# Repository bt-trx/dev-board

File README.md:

# bt-trx-dev-board

## BOM Generation

https://github.com/SchrodingersGat/KiBoM

### Installation

"Tools" -> "Generate Bill of Materials" -> New Plugin

### Benutzung

Eintragen der Bestellnummern ueber Properties des einzelnen Bauteils, oder gesammelt ueber "Tools"->"Edit Symbol Fields..."

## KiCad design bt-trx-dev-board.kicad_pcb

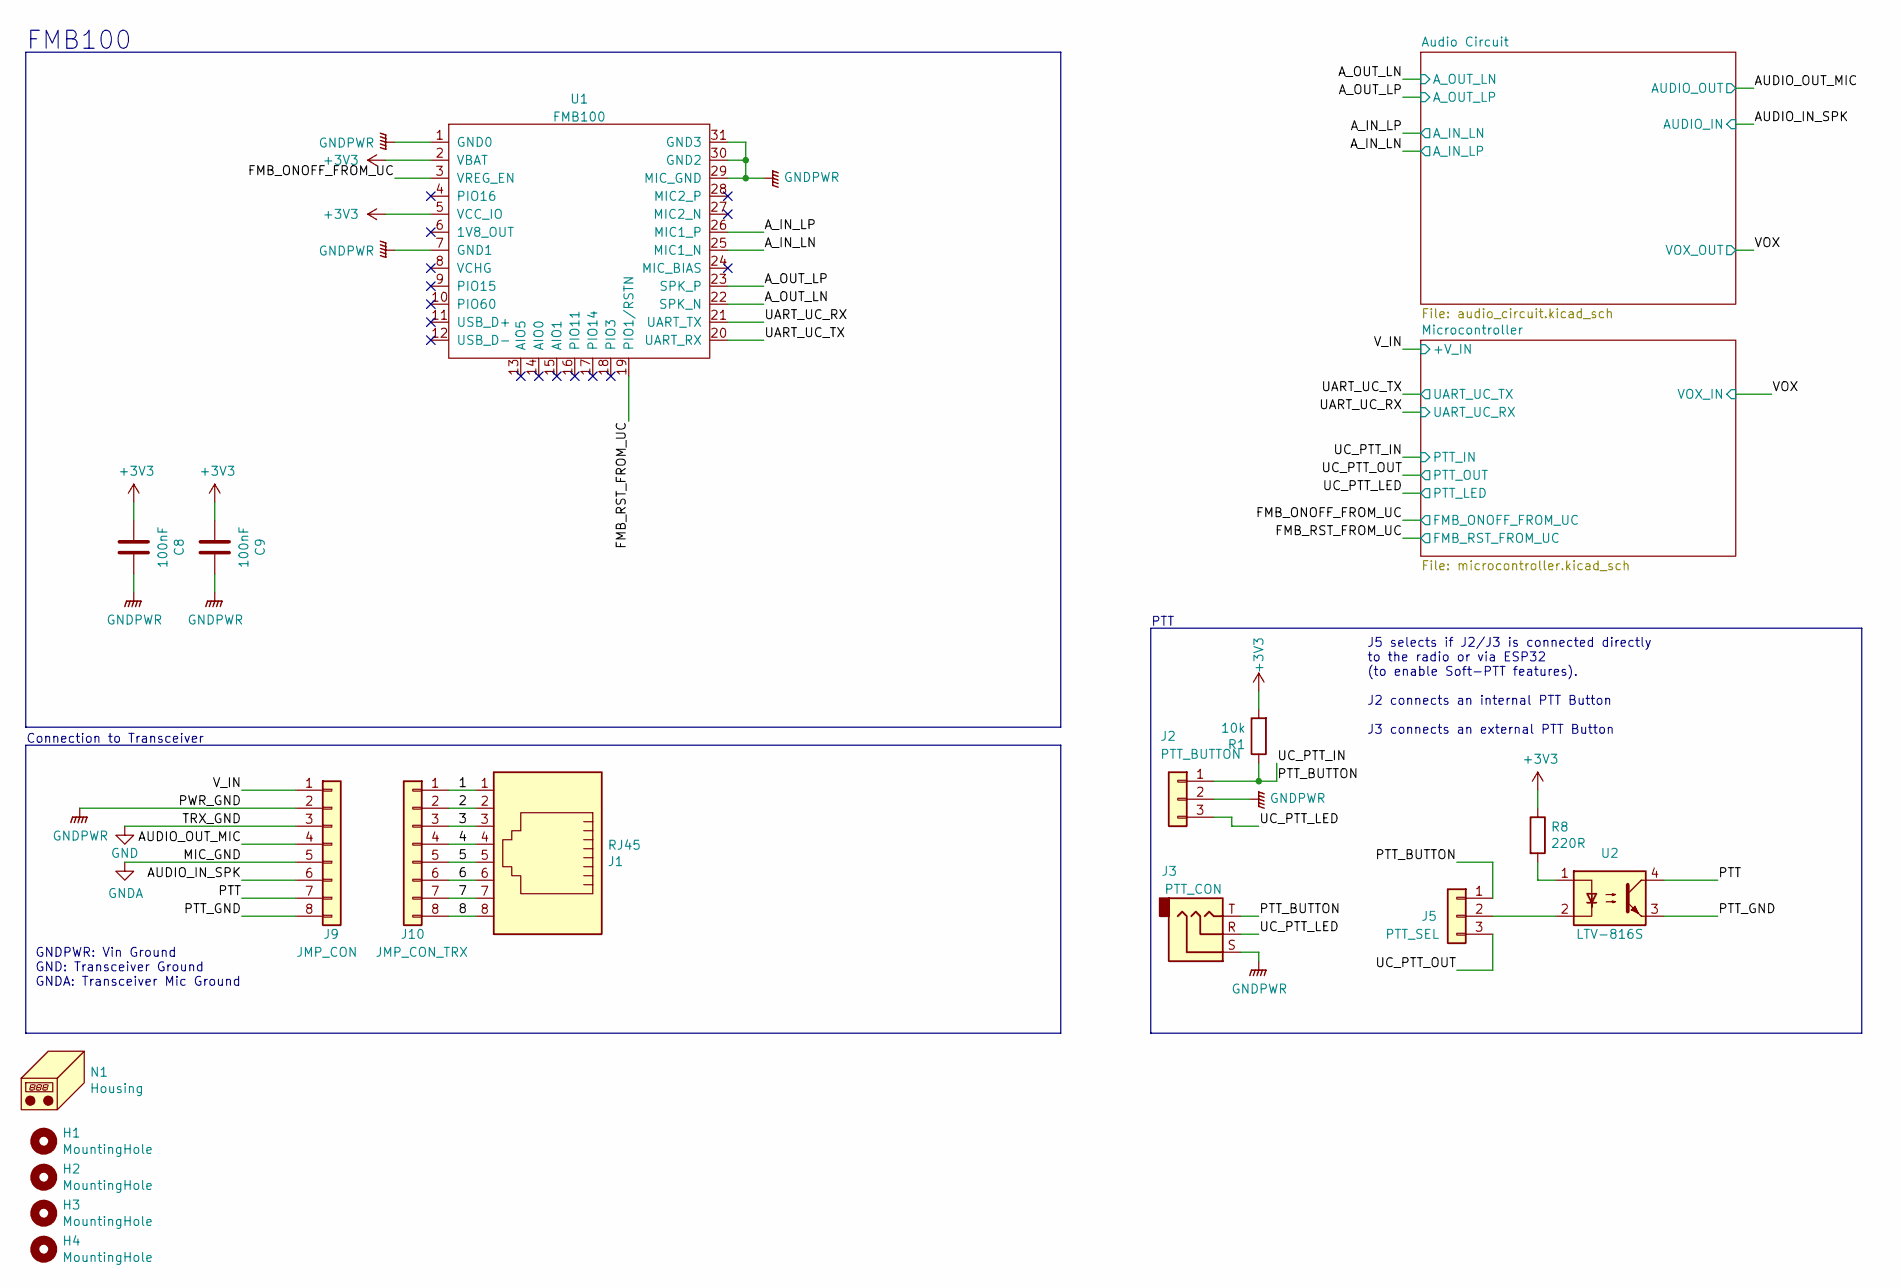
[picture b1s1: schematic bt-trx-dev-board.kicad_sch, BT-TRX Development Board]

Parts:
C8, C9: 100nF; C_0805_2012Metric_Pad1.15x1.40mm_HandSolder; PartNrDigikey 732-8080-1-ND; Mouser Best.Nr. 710-885012207098
H1, H2, H3, H4: MountingHole; MountingHole_3.2mm_M3_DIN965
J1: RJ45; RJ45_Amphenol_54602-x08_Horizontal; PartNrDigikey 609-1046-ND; Mouser Best.Nr. 649-54602-908LF
J2: PTT_BUTTON; PinHeader_1x03_P2.54mm_Vertical; PartNrDigikey 952-2264-ND; Mouser Best.Nr. 855-M20-9990346
J3: PTT_CON; Jack_3.5mm_CUI_SJ1-3533NG_Horizontal; PartNrDigikey CP1-3533NG-ND; Mouser Best.Nr. 490-SJ1-3533NG
J5: PTT_SEL; PinHeader_1x03_P2.54mm_Vertical; PartNrDigikey 952-2264-ND; Mouser Best.Nr. 855-M20-9990346
J9: JMP_CON; PinSocket_1x08_P2.54mm_Vertical; PartNrDigikey 952-1823-ND; Mouser Best.Nr. 855-M20-7820842
J10: JMP_CON_TRX; PinSocket_1x08_P2.54mm_Vertical; PartNrDigikey 952-1823-ND; Mouser Best.Nr. 855-M20-7820842
N1: Housing; OSHW-Logo2_7.3x6mm_SilkScreen; PartNrDigikey HM447-ND; Mouser Best.Nr. 546-1553CBK
R1: 10k; R_0805_2012Metric_Pad1.20x1.40mm_HandSolder; PartNrDigikey 311-10.0KCRCT-ND; Mouser Best.Nr. 603-RC0805FR-0710KL
R8: 220R; R_0805_2012Metric_Pad1.20x1.40mm_HandSolder; Mouser Best.Nr. 603-RC0805FR-10220RL
U1: FMB100
U2: LTV-816S; PartNrDigikey 160-1361-5-ND; Mouser Best.Nr. 859-LTV-816S

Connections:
+3V3: C8.2, C9.2, R1.2, R8.1, U1.2 (VBAT), U1.5 (VCC_IO); also elsewhere on the board
/1: J1.1, J10.1
/2: J1.2, J10.2
/3: J1.3, J10.3
/4: J1.4, J10.4
/5: J1.5, J10.5
/6: J1.6, J10.6
/7: J1.7, J10.7
/8: J1.8, J10.8
/AUDIO_IN_SPK: J9.6; also elsewhere on the board
/AUDIO_OUT_MIC: J9.4; also elsewhere on the board
/A_IN_LN: U1.25 (MIC1_N); also elsewhere on the board
/A_IN_LP: U1.26 (MIC1_P); also elsewhere on the board
/A_OUT_LN: U1.22 (SPK_N); also elsewhere on the board
/A_OUT_LP: U1.23 (SPK_P); also elsewhere on the board
/FMB_ONOFF_FROM_UC: U1.3 (VREG_EN); also elsewhere on the board
/FMB_RST_FROM_UC: U1.19 (PIO1/RSTN); also elsewhere on the board
/PTT: J9.7, U2.4
/PTT_BUTTON: J2.1, J3.T, J5.1, R1.1; also elsewhere on the board
/PTT_GND: J9.8, U2.3
/UART_UC_RX: U1.21 (UART_TX); also elsewhere on the board
/UART_UC_TX: U1.20 (UART_RX); also elsewhere on the board
/UC_PTT_LED: J2.3, J3.R; also elsewhere on the board
/UC_PTT_OUT: J5.3; also elsewhere on the board
/V_IN: J9.1; also elsewhere on the board
GND: J9.3; also elsewhere on the board
GNDA: J9.5; also elsewhere on the board
GNDPWR: C8.1, C9.1, J2.2, J3.S, J9.2, U1.1 (GND0), U1.7 (GND1), U1.29 (MIC_GND), U1.30 (GND2), U1.31 (GND3); also elsewhere on the board
unnamed: J5.2, U2.2
unnamed: R8.2, U2.1

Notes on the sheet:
J5 selects if J2/J3 is connected directly to the radio or via ESP32 (to enable Soft-PTT features). J2 connects an internal PTT Button J3 connects an external PTT Button
PTT
GNDPWR: Vin Ground GND: Transceiver Ground GNDA: Transceiver Mic Ground
FMB100
Connection to Transceiver

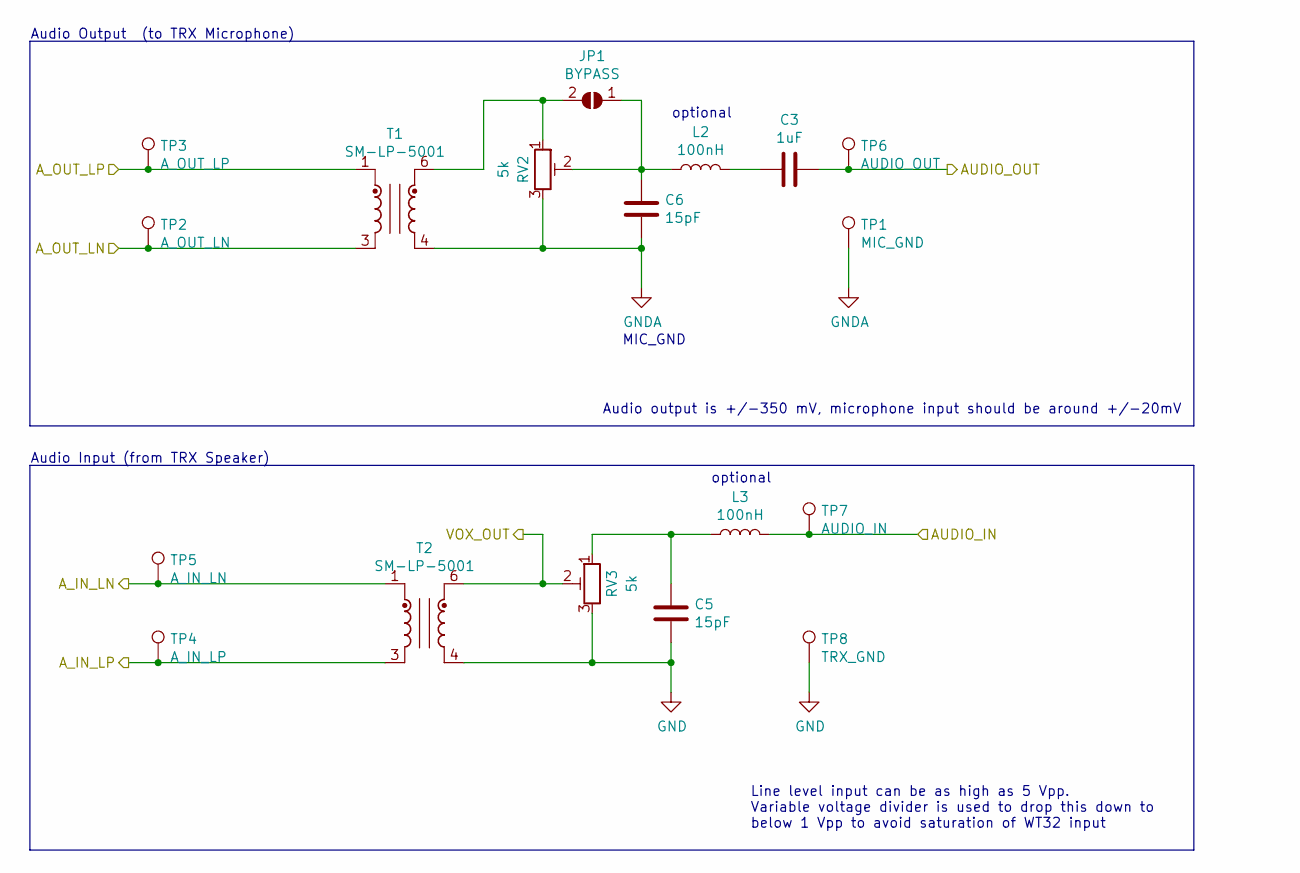
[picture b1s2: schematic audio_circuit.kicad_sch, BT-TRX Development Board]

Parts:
C3: 1uF; C_0805_2012Metric_Pad1.15x1.40mm_HandSolder; PartNrDigikey 399-6929-1-ND; Mouser Best.Nr. 80-C0805C105K3RAUTO
C5, C6: 15pF; C_0805_2012Metric_Pad1.15x1.40mm_HandSolder; PartNrDigikey 732-7815-1-ND; Mouser Best.Nr. 710-885012007011
JP1: BYPASS; SolderJumper-2_P1.3mm_Open_TrianglePad1.0x1.5mm
L2, L3: 100nH; L_0805_2012Metric_Pad1.15x1.40mm_HandSolder; PartNrDigikey 445-8983-1-ND; Mouser Best.Nr. 810-MLF2012DR10MT000
RV2, RV3: 5k; Potentiometer_Vishay_TS53YL_Vertical; PartNrDigikey TS53YL-5.0KCT-ND; Mouser Best.Nr. 72-TS53YL-5K
T1, T2: SM-LP-5001; PartNrDigikey SM-LP-5001-ND; Mouser Best.Nr. 652-SM-LP-5001
TP1: MIC_GND; TestPoint_Pad_D1.5mm
TP2: A_OUT_LN; TestPoint_Pad_D1.5mm
TP3: A_OUT_LP; TestPoint_Pad_D1.5mm
TP4: A_IN_LP; TestPoint_Pad_D1.5mm
TP5: A_IN_LN; TestPoint_Pad_D1.5mm
TP6: AUDIO_OUT; TestPoint_Pad_D1.5mm
TP7: AUDIO_IN; TestPoint_Pad_D1.5mm
TP8: TRX_GND; TestPoint_Pad_4.0x4.0mm

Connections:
/AUDIO_IN_SPK: L3.2, TP7.1; also elsewhere on the board
/AUDIO_OUT_MIC: C3.1, TP6.1; also elsewhere on the board
/A_IN_LN: T2.3, TP4.1; also elsewhere on the board
/A_IN_LP: T2.1, TP5.1; also elsewhere on the board
/A_OUT_LN: T1.3, TP2.1; also elsewhere on the board
/A_OUT_LP: T1.1, TP3.1; also elsewhere on the board
/VOX: RV3.2, T2.6; also elsewhere on the board
GND: C5.2, RV3.3, T2.4, TP8.1; also elsewhere on the board
GNDA: C6.2, RV2.3, T1.4, TP1.1; also elsewhere on the board
unnamed: C3.2, L2.2
unnamed: C5.1, L3.1, RV3.1
unnamed: C6.1, JP1.1 (A), L2.1, RV2.2
unnamed: JP1.2 (B), RV2.1, T1.6

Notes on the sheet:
Audio Output (to TRX Microphone)
Audio Input (from TRX Speaker)
Line level input can be as high as 5 Vpp. Variable voltage divider is used to drop this down to below 1 Vpp to avoid saturation of WT32 input
Audio output is +/-350 mV, microphone input should be around +/-20mV
optional
MIC_GND

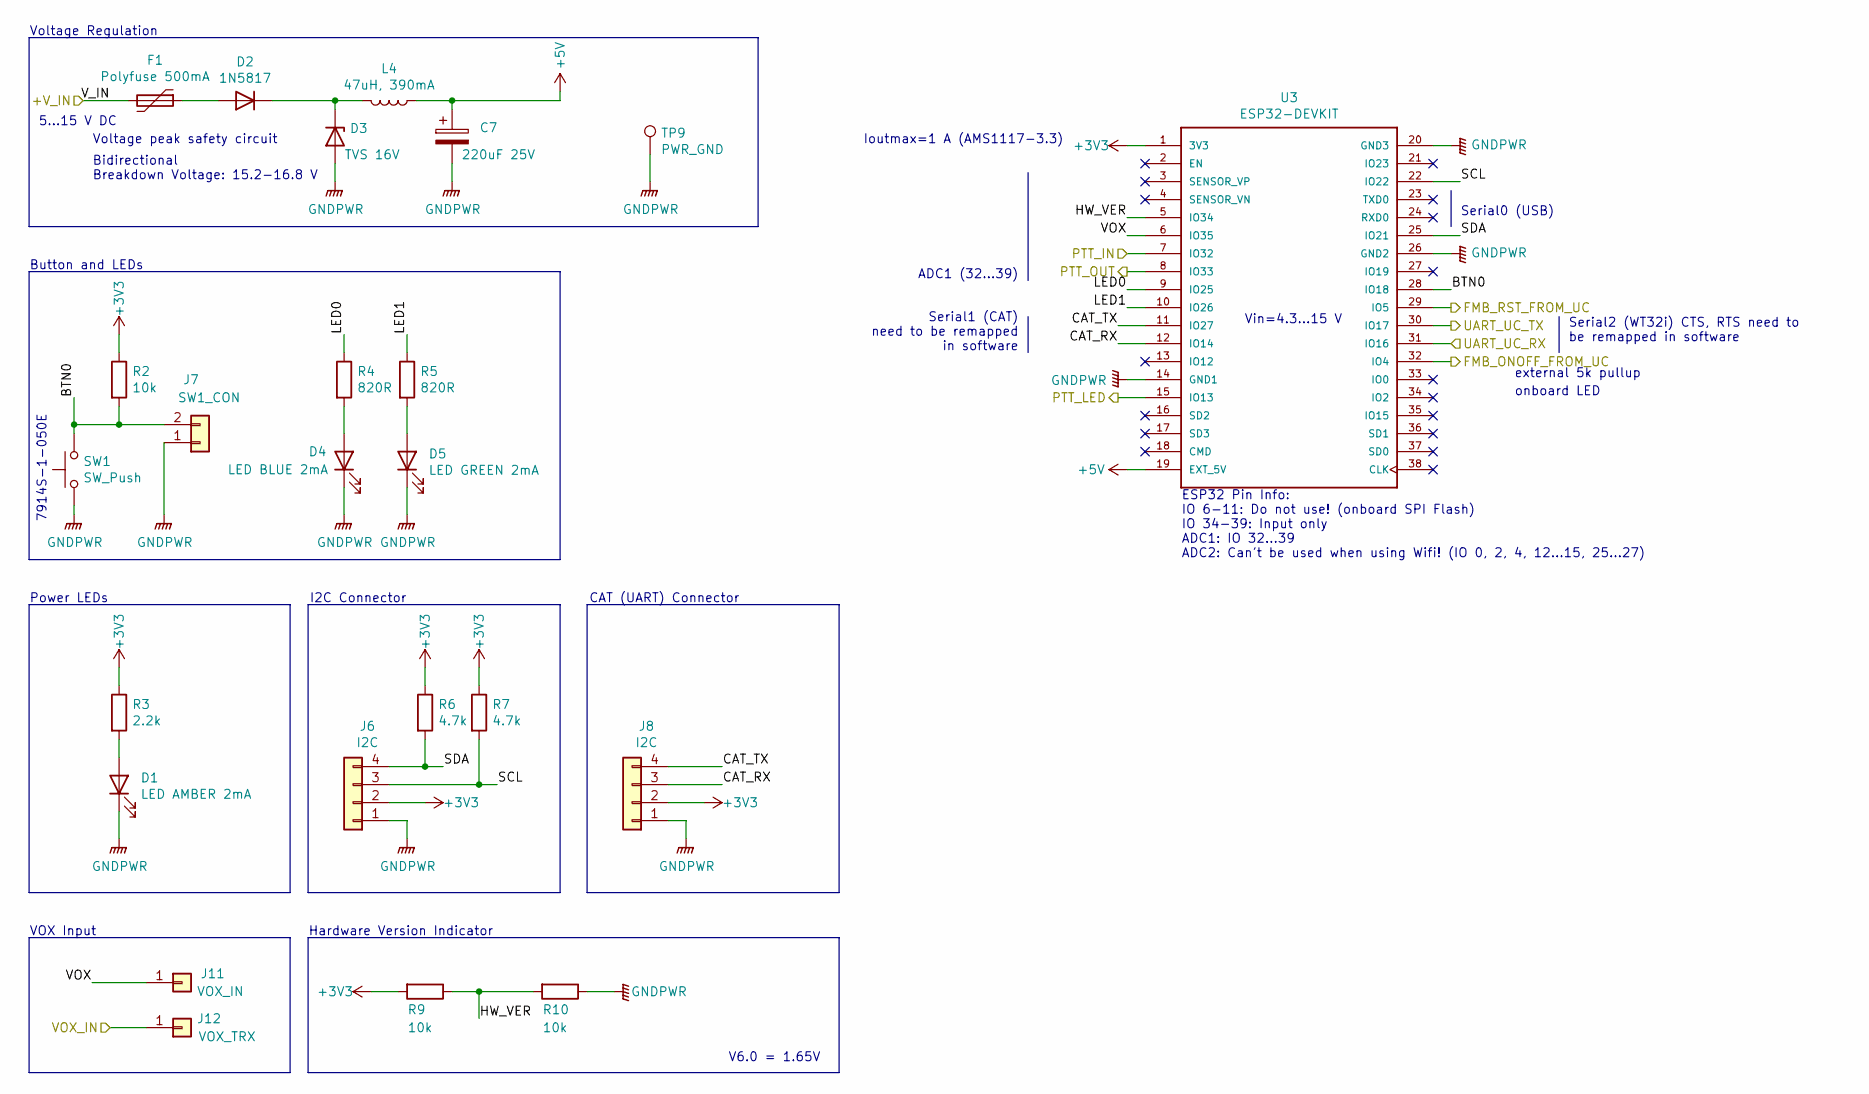
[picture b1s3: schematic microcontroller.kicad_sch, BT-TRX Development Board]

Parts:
C7: 220uF 25V; CP_Elec_10x10.5; PartNrDigikey PCE4214CT-ND; Mouser Best.Nr. 667-EEE-HA1H221P
D1: LED AMBER 2mA; APA2107LSECK; PartNrDigikey 754-1921-1-ND; Mouser Best.Nr. 604-APA2107LSECKJ4RV
D2: 1N5817; D_SMA; Mouser Best.Nr. 583-FM5817
D3: TVS 16V; D_SMB; PartNrDigikey P6SMB16CABBCT-ND; Mouser Best.Nr. 652-P6SMB16CA
D4: LED BLUE 2mA; APA2107LSECK; PartNrDigikey 754-1923-1-ND; Mouser Best.Nr. 604-APA2107LVBCD
D5: LED GREEN 2mA; APA2107LSECK; PartNrDigikey 754-1924-1-ND; Mouser Best.Nr. 604-APA2107LZGCK
F1: Polyfuse 500mA; Fuse_1206_3216Metric_Pad1.42x1.75mm_HandSolder; PartNrDigikey 507-1799-1-ND; Mouser Best.Nr. 530-0ZCJ0025AF2E
J6, J8: I2C; PinHeader_1x04_P2.54mm_Vertical; PartNrDigikey 952-1785-ND; Mouser Best.Nr. 855-M20-9770446
J7: SW1_CON; PinHeader_1x02_P2.54mm_Vertical; PartNrDigikey 952-2262-ND; Mouser Best.Nr. 855-M20-9990246
J11: VOX_IN; PinSocket_1x01_P2.54mm_Vertical
J12: VOX_TRX; PinSocket_1x01_P2.54mm_Vertical
L4: 47uH, 390mA; L_Wuerth_MAPI-3020; PartNrDigikey 732-4872-1-ND; Mouser Best.Nr. 710-74438335470
R2, R9, R10: 10k; R_0805_2012Metric_Pad1.20x1.40mm_HandSolder; PartNrDigikey 311-10.0KCRCT-ND; Mouser Best.Nr. 603-RC0805FR-0710KL
R3: 2.2k; R_0805_2012Metric_Pad1.20x1.40mm_HandSolder; PartNrDigikey 311-2.2KARCT-ND; Mouser Best.Nr. 603-RC0805JR-072K2L
R4, R5: 820R; R_0805_2012Metric_Pad1.20x1.40mm_HandSolder; PartNrDigikey 311-820ARCT-ND; Mouser Best.Nr. 603-RC0805JR-07820RL
R6, R7: 4.7k; R_0805_2012Metric_Pad1.20x1.40mm_HandSolder; PartNrDigikey 311-4.7KARCT-ND; Mouser Best.Nr. 603-RC0805JR-074K7L
SW1: SW_Push; SW_Tactile_SKHH_Angled; PartNrDigikey CKN10950-ND; Mouser Best.Nr. 611-PTS645VK832
TP9: PWR_GND; TestPoint_Pad_4.0x4.0mm
U3: ESP32-DEVKIT; ESP32-DEVKITC-32D; PartNrDigikey 1965-1000-ND; Mouser Best.Nr. 356-ESP32-DEVKITC32D

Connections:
+3V3: J6.2, J8.2, R2.1, R3.1, R6.1, R7.1, R9.2, U3.1 (3V3); also elsewhere on the board
+5V: C7.1, L4.1, U3.19 (EXT_5V)
/FMB_ONOFF_FROM_UC: U3.32 (IO4); also elsewhere on the board
/FMB_RST_FROM_UC: U3.29 (IO5); also elsewhere on the board
/Microcontroller/BTN0: J7.2, R2.2, SW1.2, U3.28 (IO18)
/Microcontroller/CAT_RX: J8.3, U3.12 (IO14)
/Microcontroller/CAT_TX: J8.4, U3.11 (IO27)
/Microcontroller/HW_VER: R9.1, R10.2, U3.5 (IO34)
/Microcontroller/LED0: R4.1, U3.9 (IO25)
/Microcontroller/LED1: R5.1, U3.10 (IO26)
/Microcontroller/SCL: J6.3, R7.2, U3.22 (IO22)
/Microcontroller/SDA: J6.4, R6.2, U3.25 (IO21)
/Microcontroller/VOX: J11.1, U3.6 (IO35)
/PTT_BUTTON: U3.7 (IO32); also elsewhere on the board
/UART_UC_RX: U3.31 (IO16); also elsewhere on the board
/UART_UC_TX: U3.30 (IO17); also elsewhere on the board
/UC_PTT_LED: U3.15 (IO13); also elsewhere on the board
/UC_PTT_OUT: U3.8 (IO33); also elsewhere on the board
/VOX: J12.1; also elsewhere on the board
/V_IN: F1.2; also elsewhere on the board
GNDPWR: C7.2, D1.1 (K), D3.2 (A), D4.1 (K), D5.1 (K), J6.1, J7.1, J8.1, R10.1, SW1.1, TP9.1, U3.14 (GND1), U3.20 (GND3), U3.26 (GND2); also elsewhere on the board
unnamed: D1.2 (A), R3.2
unnamed: D2.1 (K), D3.1 (K), L4.2
unnamed: D2.2 (A), F1.1
unnamed: D4.2 (A), R4.2
unnamed: D5.2 (A), R5.2

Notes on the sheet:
7914S-1-050E
I2C Connector
ADC1 (32...39)
Ioutmax=1 A (AMS1117-3.3)
onboard LED
Hardware Version Indicator
Voltage peak safety circuit
external 5k pullup
5...15 V DC
VOX Input
ESP32 Pin Info: IO 6-11: Do not use! (onboard SPI Flash) IO 34-39: Input only ADC1: IO 32...39 ADC2: Can't be used when using Wifi! (IO 0, 2, 4, 12...15, 25...27)
Serial2 (WT32i) CTS, RTS need to be remapped in software
Button and LEDs
Serial1 (CAT) need to be remapped in software
Voltage Regulation
V6.0 = 1.65V
Bidirectional Breakdown Voltage: 15.2-16.8 V
CAT (UART) Connector
Power LEDs
Vin=4.3...15 V
Serial0 (USB)

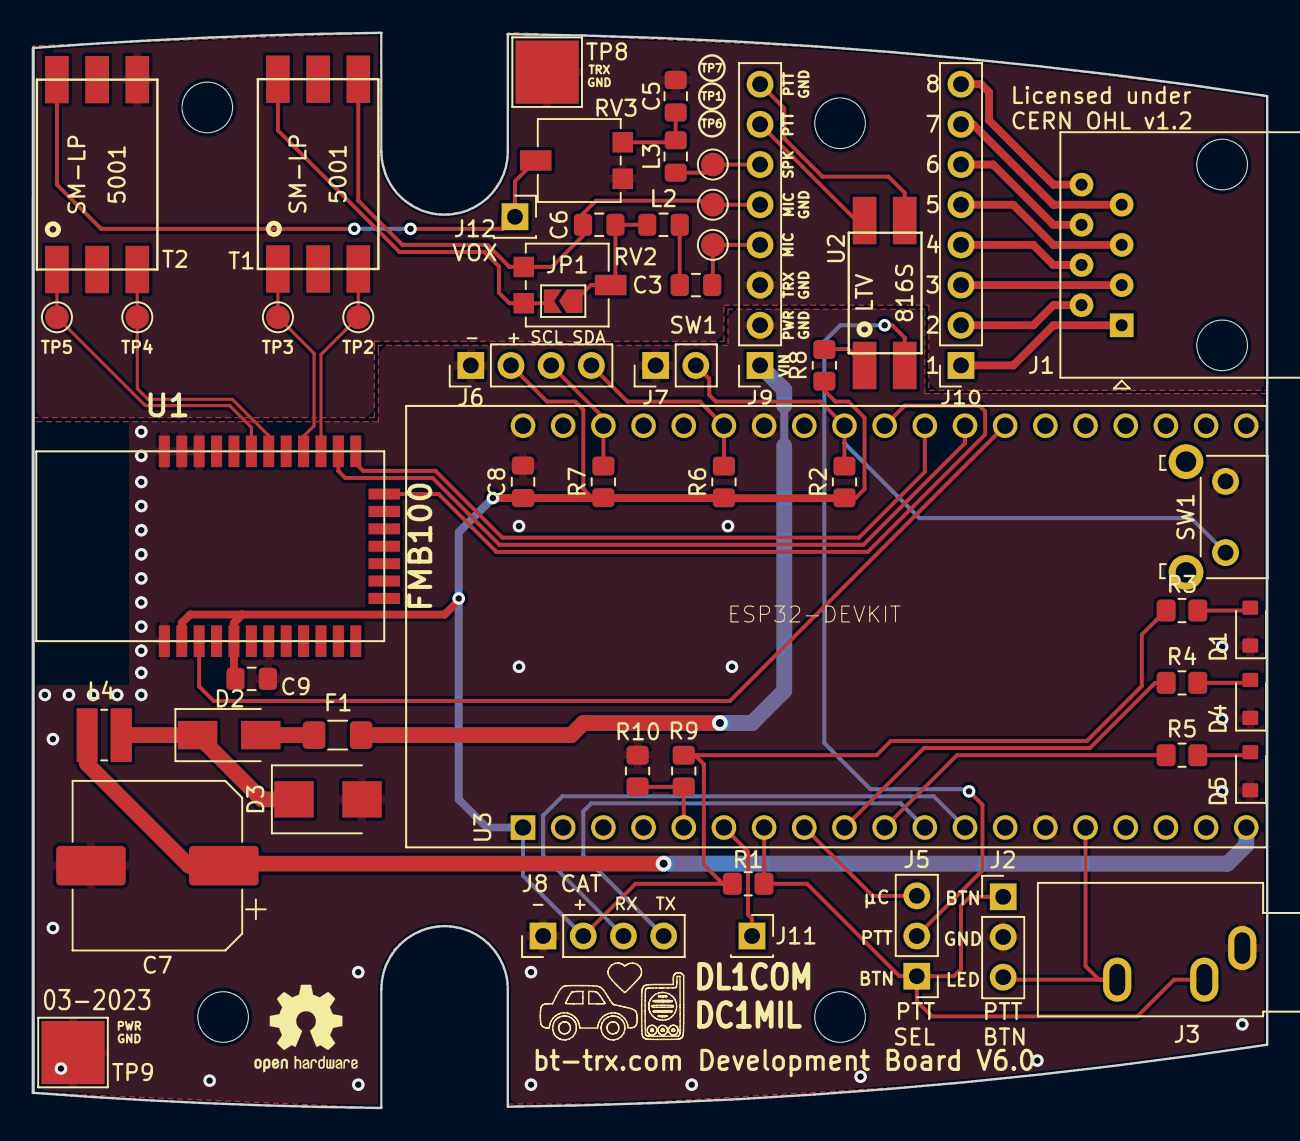
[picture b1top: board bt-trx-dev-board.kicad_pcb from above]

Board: 2 copper layers, 78.0 x 67.9 mm, 59 parts (0 on the bottom side), 50 nets.

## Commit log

2019-06-21 Squash commit of private dev repo for publication
2019-07-04 renamed audio_cirquit.sch to audio_circuit.sch
2019-07-04 Add ESP-32S symbol and footprint, start integration
2019-07-24 Assigned Pins to ESP32 and removed Teensy [#1]
2019-07-24 Continued v4 [#1]
    *removed all v3 stuff
    * Resized board to max case size
    * First deratsnesting
2019-08-06 [#1] Refined Schematic
    * Removed RTS CTS
    * Added 15pF capacitator to audio IN+
    * Removed PTT jumper
    * Added pull-up jumper
    * Added solder jmpr bypass to RV
    * Changed button footprint to SMD version
2019-08-06 [#1] Reworked audio path
    * Swaped LN and LP for better reading
    * Rearanged audio-in cirquid
2019-08-06 [#1] Deratsnested PCB
2019-08-06 [#1] Continued PCB
    * Moved button pin for better tracability
    * Added all missing traces
2019-08-06 Added fp-info-cache to .gitignore
2019-08-08 [#2] Beatufied PCB
    * Put all silkscreen items on the right place
    * Added keepout to BT antenna
    * Added couple of vias for better grounding
2019-08-08 [#6] Added 3D Models
2019-08-11 [#2] Add ESP32-NodeMCU Footprint
2019-08-11 [#2] Update Schematic with new Footprint for ESP32 Board
2019-08-11 Fix some comments
2019-08-11 [#4] Replaced wrong ESP32 package
2019-08-11 [#4] Fixed typo in version number on pcb
2019-08-11 [#3] Added new version number to sheets
2019-08-11 [#2] Moved silkscreen away from screw
2019-08-11 [#] Repacled 3D models
    * RJ45
    * Audio jack
2019-08-11 [#6] Add 3D model for ESP32 board
2019-08-11 [#6] Colored custom step models
2019-08-11 [2#] Replaced ESP 3D Model in PCB
2019-08-11 [#2] Added 3d Model for Push Button
2019-08-11 [#6] Put some color on button stepfile
2019-08-11 [#2] Added png of 3D view
2019-08-12 [#3][#4] Moved CAT pins
    Moved CAT TX and RX from pin 12/13 to pin 11/12 due to
    bootup problems with pin 13.
2019-08-13 [#5] Added Missing Parts to BOM
    * Replaced audio Cs with ceramic
    * Changed audio output DC block C to 1uF
    * Added ESP32 to BOM
2019-08-13 [#3] Removed unnecessary Text
2019-08-13 Added CHANGELOG.md
2019-08-13 Generated gerber-files for order
2019-08-13 Added BOM
2019-09-27 [#7] Connected Ring of J3 to GPIO32
    * Warning: Needed to move PTT_IN from GPIO32 to GPIO35
2019-09-27 [#8] Added solder contacts for external Button SW1
2019-09-27 [#9] Remove D6
2019-09-27 [#10] Move F1 to V_IN
2019-09-27 [#12] Change footprint of ESP32 to devkitc
    * Converted mod file to kicat_mod
    * Replaced Footprint in schematic
2019-09-27 [#13] Add Hardware Version Indicator
    Pull GPIO34 to GND to indicate v4.1
2019-09-27 [#7][#8][#9][#10][#12][#13] Created PCB V4.1
    * Change footprint to DevKitC
    * Connect Ring contact of J3 to a GPIO
    * Add solder connector for SW1
    * Remove D6
    * Move F1 to VIN
    * Add Hardware Version Indicator
2019-09-27 Replaced 3D view image
2019-09-27 Removed unused 3D Models
2019-09-27 [#11] Connected Audio to ESP Pin
    * Connected Audio Input to GPIO15 in schematic and PCB
    * Added Solder Jumper
2019-09-27 Changed Version and Date on Sheets
2019-09-27 Changed Silkscreen a bit
2019-09-28 Adding annotations for ADC1/2
2019-09-29 [#15] Replaced PTT Pullup Jumper wit Solder Jumper
2019-09-29 [#16] Move SW1 and VOX to usable Pins
    * Moved SW1 form GPIO0 to GPIO18
    * Added Pullup to SW1
    * Moved VOX form GPIO2 to GPIO35
2019-10-06 [#17] Add PTT_LED to J2 and move J2 near/behind J3
2019-10-06 [#18] Changed SW1 from SMD to TH
2019-10-06 Created BOM
2019-10-06 Changed BOM due to availability
2019-10-06 Generated Gerber files
2019-10-06 Replaced ESP32 DevKitC in BOM
2019-10-06 Added 3D view image
2019-10-06 Changelog update
2019-11-04 [#20] Fix orientation of J1 symbol in schematic
2020-01-04 [#22] Insert Optocoupler for PTT
2020-01-04 [#23] Remove AUDIO_IN_B
2020-01-15 Audio Rework in Schematic [#21]
2020-01-15 Further Audio Rework, separation of AGND and MIC_GND [#21]
2020-01-16 Continued Schematic for V5.0
    * Rearanged RJ45 connector
    * Added jumper wire connector
    * Renamed GNDs
2020-01-16 Added Footprints [#21]
    * Footprint LTV-816S
    * Footprint SML-P-5001
2020-01-16 Replaced PTT-SEL with solder jumper [#21]
    * Replaced PTT-SEL with solder jumper
    * Fixed typos in comments
2020-01-16 Fixed Typos and Missing Footprints [#21]
2020-01-18 Fixed wrong footprint C1 [#21]
2020-01-19 Continued V5.0 Schematic Rework [#21]
    - Replaced PTT_SEL Jumper from solder to pinheader
    - Added blockin capacitors to WT32i
    - Removed J9/10 solder jumpers
    - Added separate PTT GND
    - Changed hardware version indicator to 3.3V
2020-01-20 Reworked PCB [#19][#21][#22][#23]
    * Reworked PCB with new v5.0 schematic
    * Fixed position of mounting holes
2020-01-20 Add VIAs on test points for better alignment [#21]
2020-01-20 Minor changes in silkscreen [#21]
2020-01-21 Added Pullup to HW indicator [#25]
2020-01-21 Flipped T2 for better grounding [#25]
    * Flipped input ports of T2 as there as no direct TRX-GND path from RV3 to T2
2020-01-21 Updated libraries for bourns and liteon
    * Added marking for pin 1
    * Added 3D Model
2020-01-22 PCB enhancements [#25]
    * Removed C1 and C2
    * Modified symmetric audio path
    * Modified VOX path
2020-01-22 Moved libraries to project specific lib table
2020-01-22 BOM Update
2020-01-22 Generated Gerber [#28]
2020-01-22 removed RV2 from order list
2020-01-25 Silkscreen optimization
    * Added pin description to J9 and J10
    * Optimized some Silkscreen positions
2020-01-25 Updated release note
2020-01-29 Fixed mouser order IDs
2020-01-29 Re-plotted gerber files for production
2020-03-03 Fixed wrong Parts in BOM (R8, C8, C9)
2020-03-03 Add Digikey Part Numbers
2020-03-03 Remove Reichelt Part Nrs from BOM Export
2020-03-03 Update BOM Export
2020-03-16 Add default config options to bom.ini
2020-06-08 Add github actions for automatic export
2023-03-28 am: Added FBM100 lib to kicad project
2023-03-28 am: Added FMB100 to schematic
    * removed WT32i
    * replaced with FMB100
2023-03-28 anm: Added FMB100 to PCB
    * Replaced WT32i with FMB100
    * Swapped RX and TX transformers
    * Removed MIC Bias C
2023-03-28 am: fixed #30 Suboptimal placement of D3
    * Swapped D3 and L4 according to Issue #30
2023-03-28 am: updated version and date in schematic
2023-04-01 am: Modified HW indication voltage
    * Added R10 for voltage divider (v6.x == 1.65V)
    * Replaced all R footprints with current ones from KiCad lib
2023-04-01 am: Connected FMB100 RST pin to ESP
    * Connected FMB100 RST pin to ESP in schematic and PCB
2023-04-01 am: refinded .gitignore
2023-04-01 am: updated date on pcb
2023-04-01 am: removed kicad 5.0 files
2023-04-01 am: updated changelog
2023-04-01 am: refinded silkscreen
2023-04-01 am: refined silkscreen

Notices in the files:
audio_circuit.kicad_sch:
Licensed under CERN OHL v1.2 - https://ohwr.org/licenses/cern-ohl/v1.2
bt-trx-dev-board.kicad_pcb:
CERN OHL v1.2
